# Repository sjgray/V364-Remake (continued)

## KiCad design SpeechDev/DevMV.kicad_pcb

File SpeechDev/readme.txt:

Commodore V364 Prototype Remake Project   Steve J. Gray
=======================================

This is a project to remake the V364 prototype computer from Commodore.
This would have been the flagship model in the TED/264 series, and
would feature a larger case with numeric keypad and built-in speech
synthesis using a more integrated version of the Magic Voice ("MV")
cartridge that was released for the C64.

SPEECH DEV BOARD
================

This is a development board that lets you experiment with adding speech to
any 264-series machine. It contains sockets for developing either type of
speech method:

* V364 - Uses V364 custom Gate Array and the Toshiba T6721A chips
* Magic Voice - Uses 6525 TPI, GI Logic Array and T6721A chips.

**** IMPORTANT!!! Install only the chips in the correct set!

CONNECTIONS
===========

The board is connected to one ROM socket of the 264 machine via a ribbon cable,
or using a header under the board (depending on computer and clearance).
The ROM from the computer is installed on the Dev board and the V364 Speech ROM
or modified speech ROM are installed in the other socket.

There are a bunch of flyouts to connect to various places on the computer pcb.

PLA F0 - The PLA F0 pin controls the 6525 or Custom Gate Array
CS_SPEECH - Connects to ROM control C2_HI.
R/W - Connect to Read/Write line.
PHI0 - Connect to PHI0 line.
IRQ - Connect to IRQ line.
AUDIO_IN - Normally not used but can connect to a SID board etc
AUDIO_OUT - Connects to EXT_AUDIO line (cartridge connector)

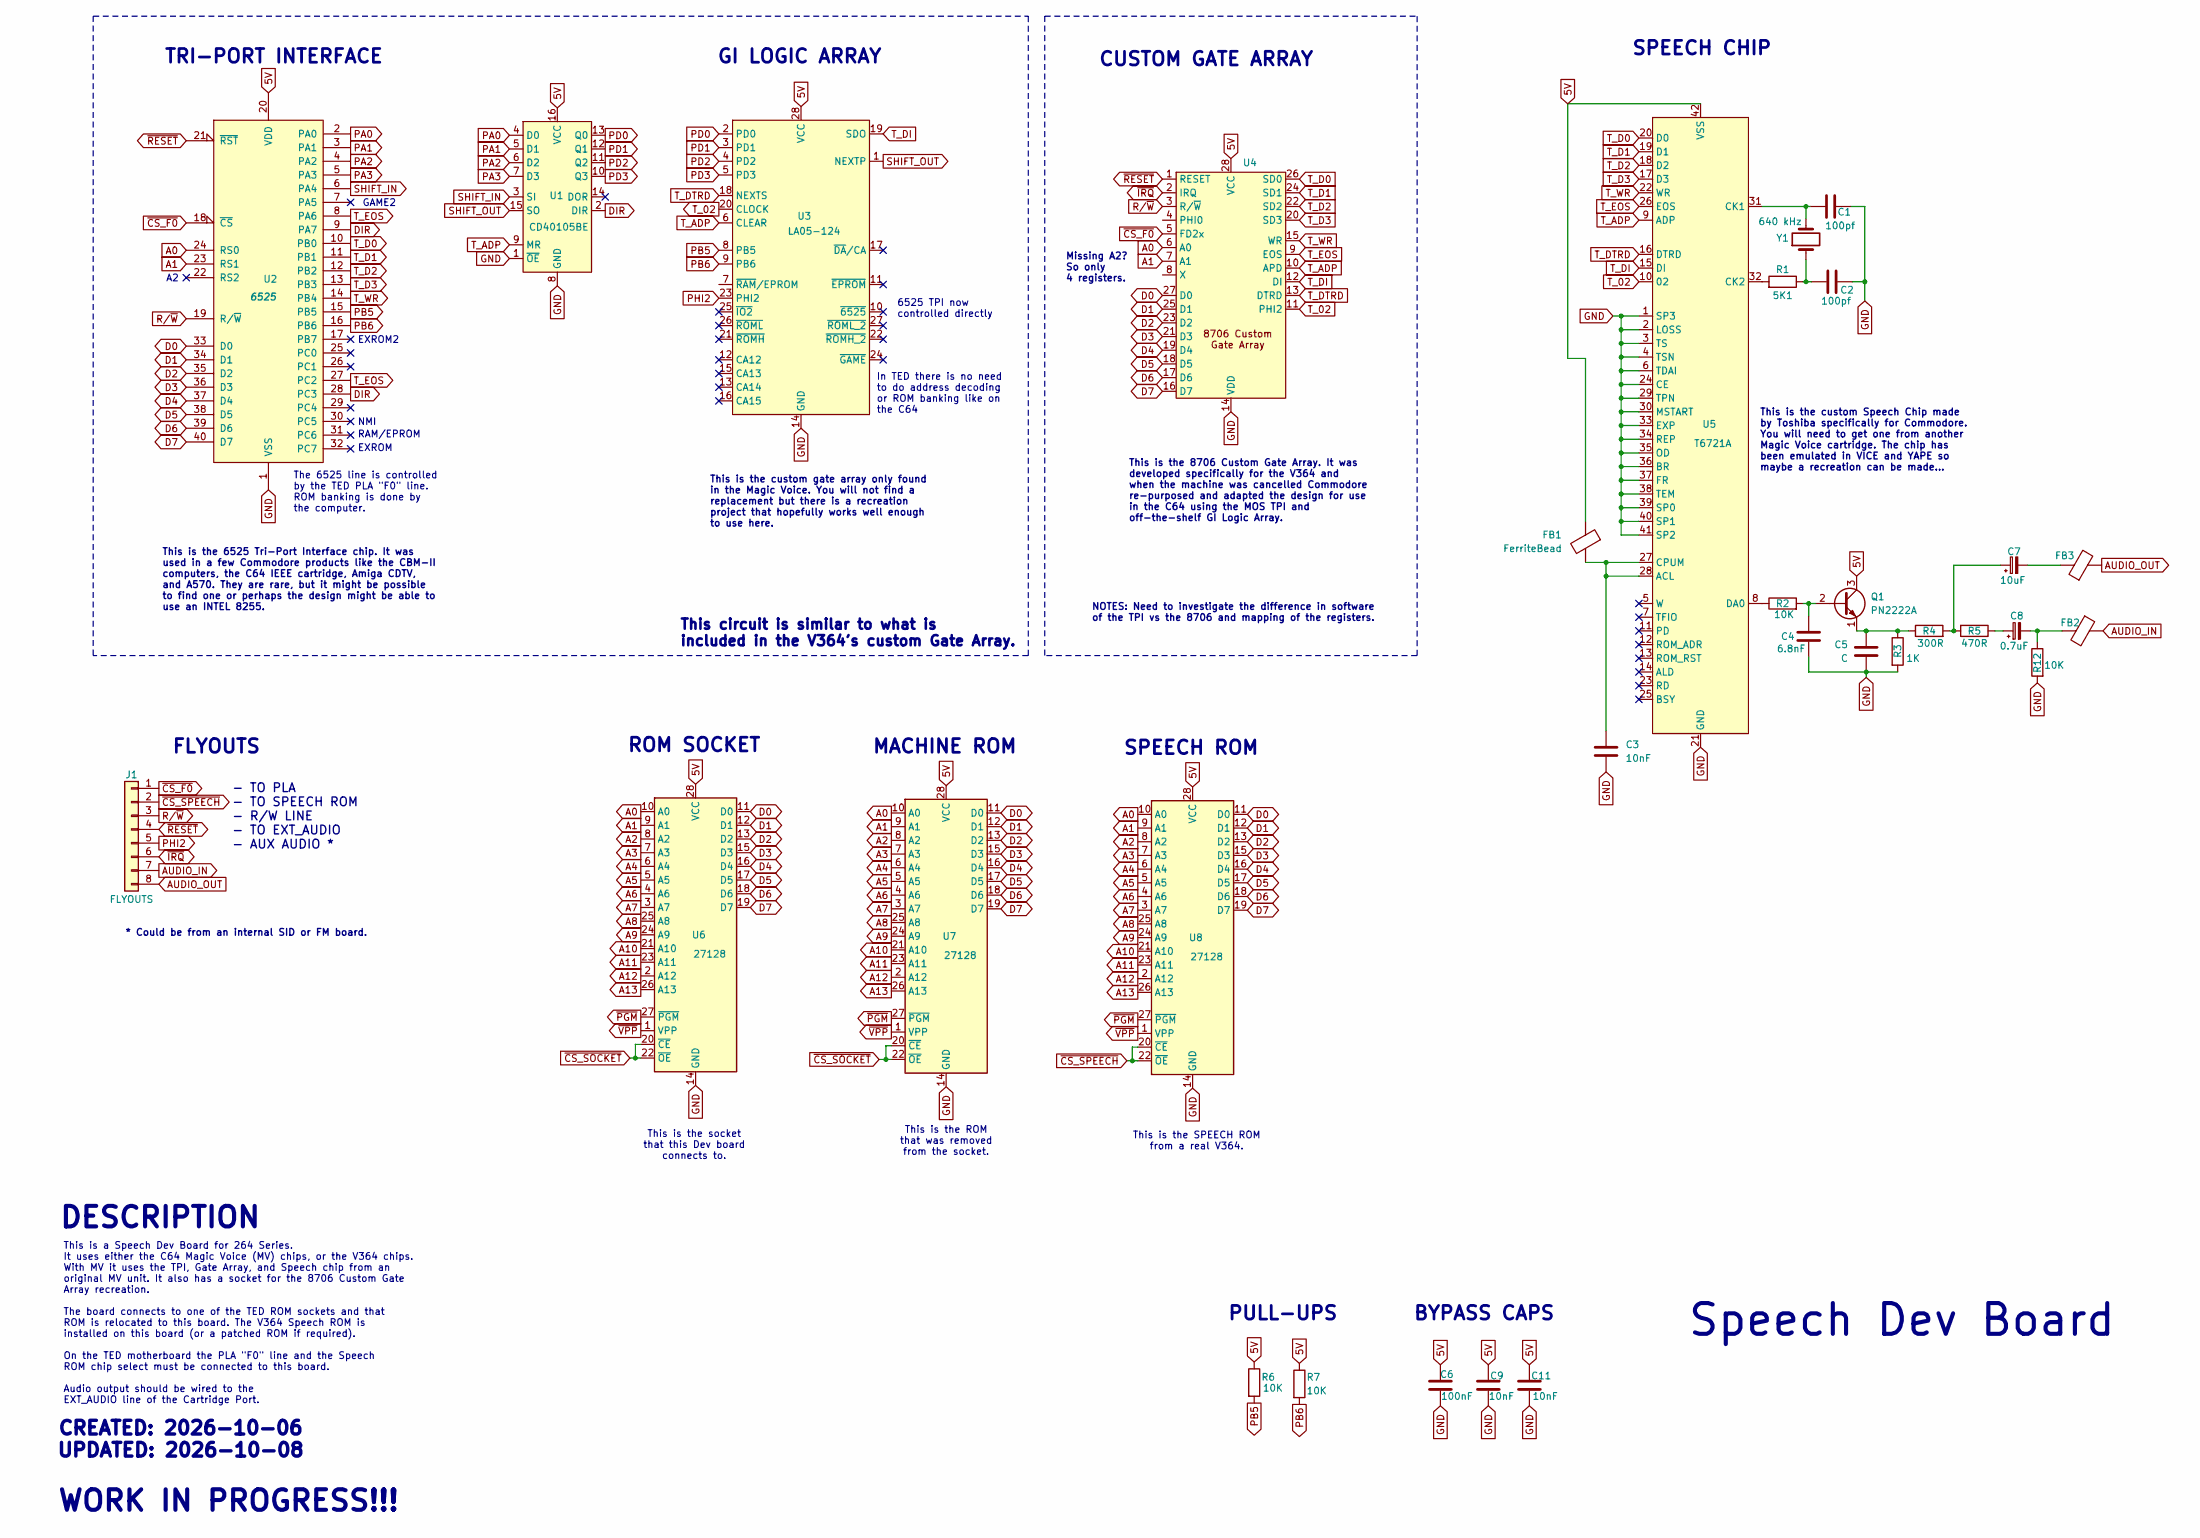
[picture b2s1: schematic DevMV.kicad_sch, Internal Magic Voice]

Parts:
C1, C2: 100pf; C_Disc_D5.0mm_W2.5mm_P5.00mm
C3, C11: 10nF; C_Disc_D5.1mm_W3.2mm_P5.00mm
C4: 6.8nF; C_Disc_D5.0mm_W2.5mm_P5.00mm
C5: C; C_Disc_D5.1mm_W3.2mm_P5.00mm
C6: 100nF; C_Disc_D5.1mm_W3.2mm_P5.00mm
C7: 10uF; CP_Radial_D8.0mm_P5.00mm
C8: 0.7uF; CP_Radial_D8.0mm_P5.00mm
C9: 10nF; C_Disc_D5.0mm_W2.5mm_P5.00mm
FB1, FB2, FB3: FerriteBead; R_Axial_DIN0309_L9.0mm_D3.2mm_P12.70mm_Horizontal
J1: FLYOUTS; PinHeader_1x08_P2.54mm_Vertical
Q1: PN2222A; TO-92_Inline_Wide
R1: 5K1; R_Axial_DIN0309_L9.0mm_D3.2mm_P12.70mm_Horizontal
R2, R6, R7, R12: 10K; R_Axial_DIN0309_L9.0mm_D3.2mm_P12.70mm_Horizontal
R3: 1K; R_Axial_DIN0309_L9.0mm_D3.2mm_P12.70mm_Horizontal
R4: 300R; R_Axial_DIN0309_L9.0mm_D3.2mm_P12.70mm_Horizontal
R5: 470R; R_Axial_DIN0309_L9.0mm_D3.2mm_P12.70mm_Horizontal
U1: CD40105BE; DIP-16_W7.62mm
U2: 6525; DIP-40_W15.24mm
U3: LA05-124; DIP-28_W15.24mm
U4: DIP-28_W15.24mm_LongPads
U5: T6721A; DIP-42_W15.24mm
U6, U7, U8: 27128; DIP-28_W15.24mm
Y1: 640 kHz; Crystal_HC18-U_Vertical

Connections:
5V: C6.1, C9.1, C11.1, FB1.1, Q1.3 (C), R6.1, R7.1, U1.16 (VCC), U2.20 (VDD), U3.28 (VCC), U4.28 (VCC), U5.42 (VSS), U6.28 (VCC), U7.28 (VCC), U8.28 (VCC)
A0: U2.24 (RS0), U4.6 (A0), U6.10 (A0), U7.10 (A0), U8.10 (A0)
A1: U2.23 (RS1), U4.7 (A1), U6.9 (A1), U7.9 (A1), U8.9 (A1)
A2: U6.8 (A2), U7.8 (A2), U8.8 (A2)
A3: U6.7 (A3), U7.7 (A3), U8.7 (A3)
A4: U6.6 (A4), U7.6 (A4), U8.6 (A4)
A5: U6.5 (A5), U7.5 (A5), U8.5 (A5)
A6: U6.4 (A6), U7.4 (A6), U8.4 (A6)
A7: U6.3 (A7), U7.3 (A7), U8.3 (A7)
A8: U6.25 (A8), U7.25 (A8), U8.25 (A8)
A9: U6.24 (A9), U7.24 (A9), U8.24 (A9)
A10: U6.21 (A10), U7.21 (A10), U8.21 (A10)
A11: U6.23 (A11), U7.23 (A11), U8.23 (A11)
A12: U6.2 (A12), U7.2 (A12), U8.2 (A12)
A13: U6.26 (A13), U7.26 (A13), U8.26 (A13)
AUDIO_IN: FB2.1, J1.7
AUDIO_OUT: FB3.2, J1.8
D0: U2.33 (D0), U4.27 (D0), U6.11 (D0), U7.11 (D0), U8.11 (D0)
D1: U2.34 (D1), U4.25 (D1), U6.12 (D1), U7.12 (D1), U8.12 (D1)
D2: U2.35 (D2), U4.23 (D2), U6.13 (D2), U7.13 (D2), U8.13 (D2)
D3: U2.36 (D3), U4.21 (D3), U6.15 (D3), U7.15 (D3), U8.15 (D3)
D4: U2.37 (D4), U4.19 (D4), U6.16 (D4), U7.16 (D4), U8.16 (D4)
D5: U2.38 (D5), U4.18 (D5), U6.17 (D5), U7.17 (D5), U8.17 (D5)
D6: U2.39 (D6), U4.17 (D6), U6.18 (D6), U7.18 (D6), U8.18 (D6)
D7: U2.40 (D7), U4.16 (D7), U6.19 (D7), U7.19 (D7), U8.19 (D7)
DIR: U1.2 (DIR), U2.9 (PA7), U2.28 (PC3)
GND: C1.1, C2.1, C3.2, C4.2, C5.2, C6.2, C9.2, C11.2, R3.2, R12.2, U1.1 (~OE), U1.8 (GND), U2.1 (VSS), U3.14 (GND), U4.14 (VDD), U5.1 (SP3), U5.2 (LOSS), U5.3 (TS), U5.4 (TSN), U5.6 (TDAI), U5.21 (GND), U5.24 (CE), U5.29 (TPN), U5.30 (MSTART), U5.33 (EXP), U5.34 (REP), U5.35 (OD), U5.36 (BR), U5.37 (FR), U5.38 (TEM), U5.39 (SP0), U5.40 (SP1), U5.41 (SP2), U6.14 (GND), U7.14 (GND), U8.14 (GND)
unnamed: C2.2, R1.1, Y1.1
unnamed: C7.1, R4.2, R5.2
unnamed: C7.2, FB3.1
unnamed: C8.1, R5.1
unnamed: C8.2, FB2.2, R12.1
unnamed: C4.1, Q1.2 (B), R2.2
unnamed: C5.1, Q1.1 (E), R3.1, R4.1
unnamed: C3.1, FB1.2, U5.27 (CPUM), U5.28 (ACL)
unnamed: C1.2, U5.31 (CK1), Y1.2
unnamed: R1.2, U5.32 (CK2)
unnamed: R2.1, U5.8 (DA0)
PA0: U1.4 (D0), U2.2 (PA0)
PA1: U1.5 (D1), U2.3 (PA1)
PA2: U1.6 (D2), U2.4 (PA2)
PA3: U1.7 (D3), U2.5 (PA3)
PB5: R6.2, U2.15 (PB5), U3.8 (PB5)
PB6: R7.2, U2.16 (PB6), U3.9 (PB6)
PD0: U1.13 (Q0), U3.2 (PD0)
PD1: U1.12 (Q1), U3.3 (PD1)
PD2: U1.11 (Q2), U3.4 (PD2)
PD3: U1.10 (Q3), U3.5 (PD3)
PHI2: J1.5, U3.23 (PHI2)
R/~W: J1.3, U2.19 (R/~W), U4.3 (R/~W)
SHIFT_IN: U1.3 (SI), U2.6 (PA4)
SHIFT_OUT: U1.15 (SO), U3.1 (NEXTP)
T_02: U3.20 (CLOCK), U4.11 (PHI2), U5.10 (02)
T_ADP: U1.9 (MR), U3.6 (CLEAR), U4.10 (APD), U5.9 (ADP)
T_D0: U2.10 (PB0), U4.26 (SD0), U5.20 (D0)
T_D1: U2.11 (PB1), U4.24 (SD1), U5.19 (D1)
T_D2: U2.12 (PB2), U4.22 (SD2), U5.18 (D2)
T_D3: U2.13 (PB3), U4.20 (SD3), U5.17 (D3)
T_DI: U3.19 (SDO), U4.12 (DI), U5.15 (DI)
T_DTRD: U3.18 (NEXTS), U4.13 (DTRD), U5.16 (DTRD)
T_EOS: U2.8 (PA6), U2.27 (PC2), U4.9 (EOS), U5.26 (EOS)
T_WR: U2.14 (PB4), U4.15 (WR), U5.22 (WR)
~CS_F0: J1.1, U2.18 (~CS), U4.5 (FD2x)
~CS_SOCKET: U6.20 (~CE), U6.22 (~OE), U7.20 (~CE), U7.22 (~OE)
~CS_SPEECH: J1.2, U8.20 (~CE), U8.22 (~OE)
~IRQ: J1.6, U4.2 (IRQ)
~PGM: U6.27 (~PGM), U7.27 (~PGM), U8.27 (~PGM)
~RESET: J1.4, U2.21 (~RST), U4.1 (RESET)
~VPP: U6.1 (VPP), U7.1 (VPP), U8.1 (VPP)

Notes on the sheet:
FLYOUTS
The 6525 line is controlled by the TED PLA "F0" line. ROM banking is done by the computer.
This is a Speech Dev Board for 264 Series. It uses either the C64 Magic Voice (MV) chips, or the V364 chips. With MV it uses the TPI, Gate Array, and Speech chip from an original MV unit. It also has a socket for the 8706 Custom Gate Array recreation. The board connects to one of the TED ROM socket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
This circuit is similar to what is included in the V364's custom Gate Array.
This is the SPEECH ROM from a real V364.
WORK IN PROGRESS!!!
Speech Dev Board
CUSTOM GATE ARRAY
TRI-PORT INTERFACE
GI LOGIC ARRAY
This is the custom gate array only found in the Magic Voice. You will not find a replacement but there is a recreation project that hopefully works well enough to use here.
This is the 8706 Custom Gate Array. It was developed specifically for the V364 and when the machine was cancelled Commodore re-purposed and adapted the design for use in the C64 using the MOS TPI and off-the-shelf GI Logic Array.
EXROM2
BYPASS CAPS
EXROM
ROM SOCKET
- TO PLA - TO SPEECH ROM - R/W LINE - TO EXT_AUDIO - AUX AUDIO *
MACHINE ROM
Missing A2? So only 4 registers.
RAM/EPROM
SPEECH ROM
This is the custom Speech Chip made by Toshiba specifically for Commodore. You will need to get one from another Magic Voice cartridge. The chip has been emulated in VICE and YAPE so maybe a recreation can be made...
* Could be from an internal SID or FM board.
PULL-UPS
NOTES: Need to investigate the difference in software of the TPI vs the 8706 and mapping of the registers.
SPEECH CHIP
6525 TPI now controlled directly
NMI
CREATED: 2026-10-06 UPDATED: 2026-10-08
This is the socket that this Dev board connects to.
DESCRIPTION
This is the ROM that was removed from the socket.
This is the 6525 Tri-Port Interface chip. It was used in a few Commodore products like the CBM-II computers, the C64 IEEE cartridge, Amiga CDTV, and A570. They are rare, but it might be possible to find one or perhaps the design might be able to use an INTEL 8255.
In TED there is no need to do address decoding or ROM banking like on the C64
GAME2

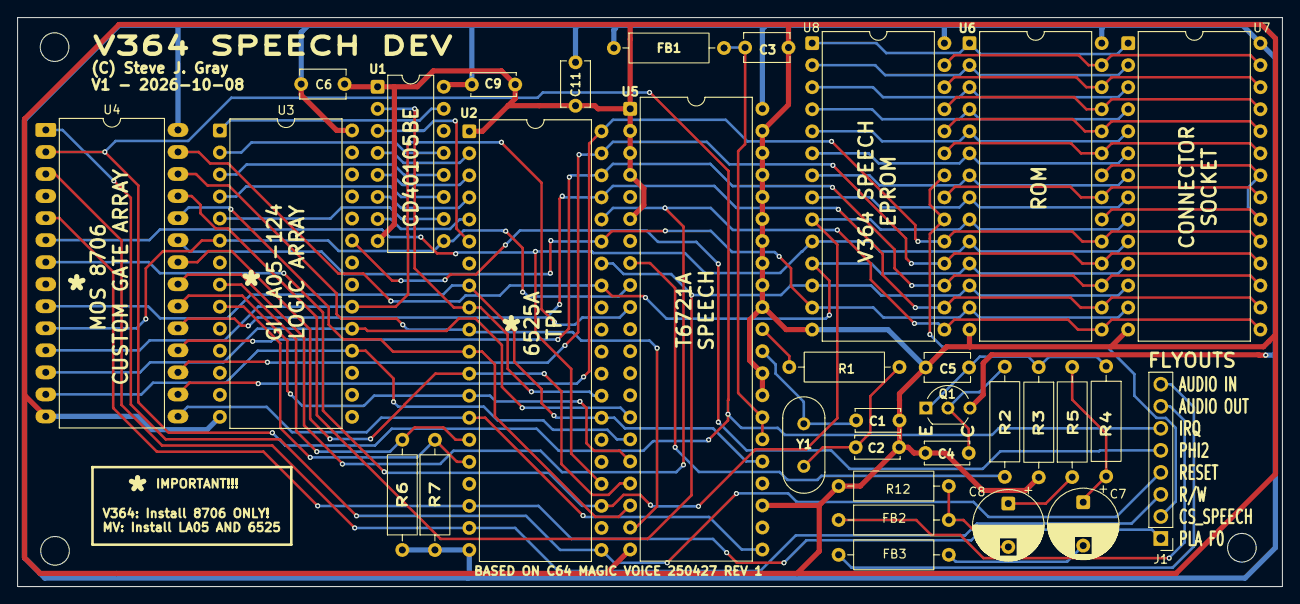
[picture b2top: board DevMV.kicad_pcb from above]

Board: 2 copper layers, 145.8 x 65.6 mm, 32 parts (0 on the bottom side), 69 nets.

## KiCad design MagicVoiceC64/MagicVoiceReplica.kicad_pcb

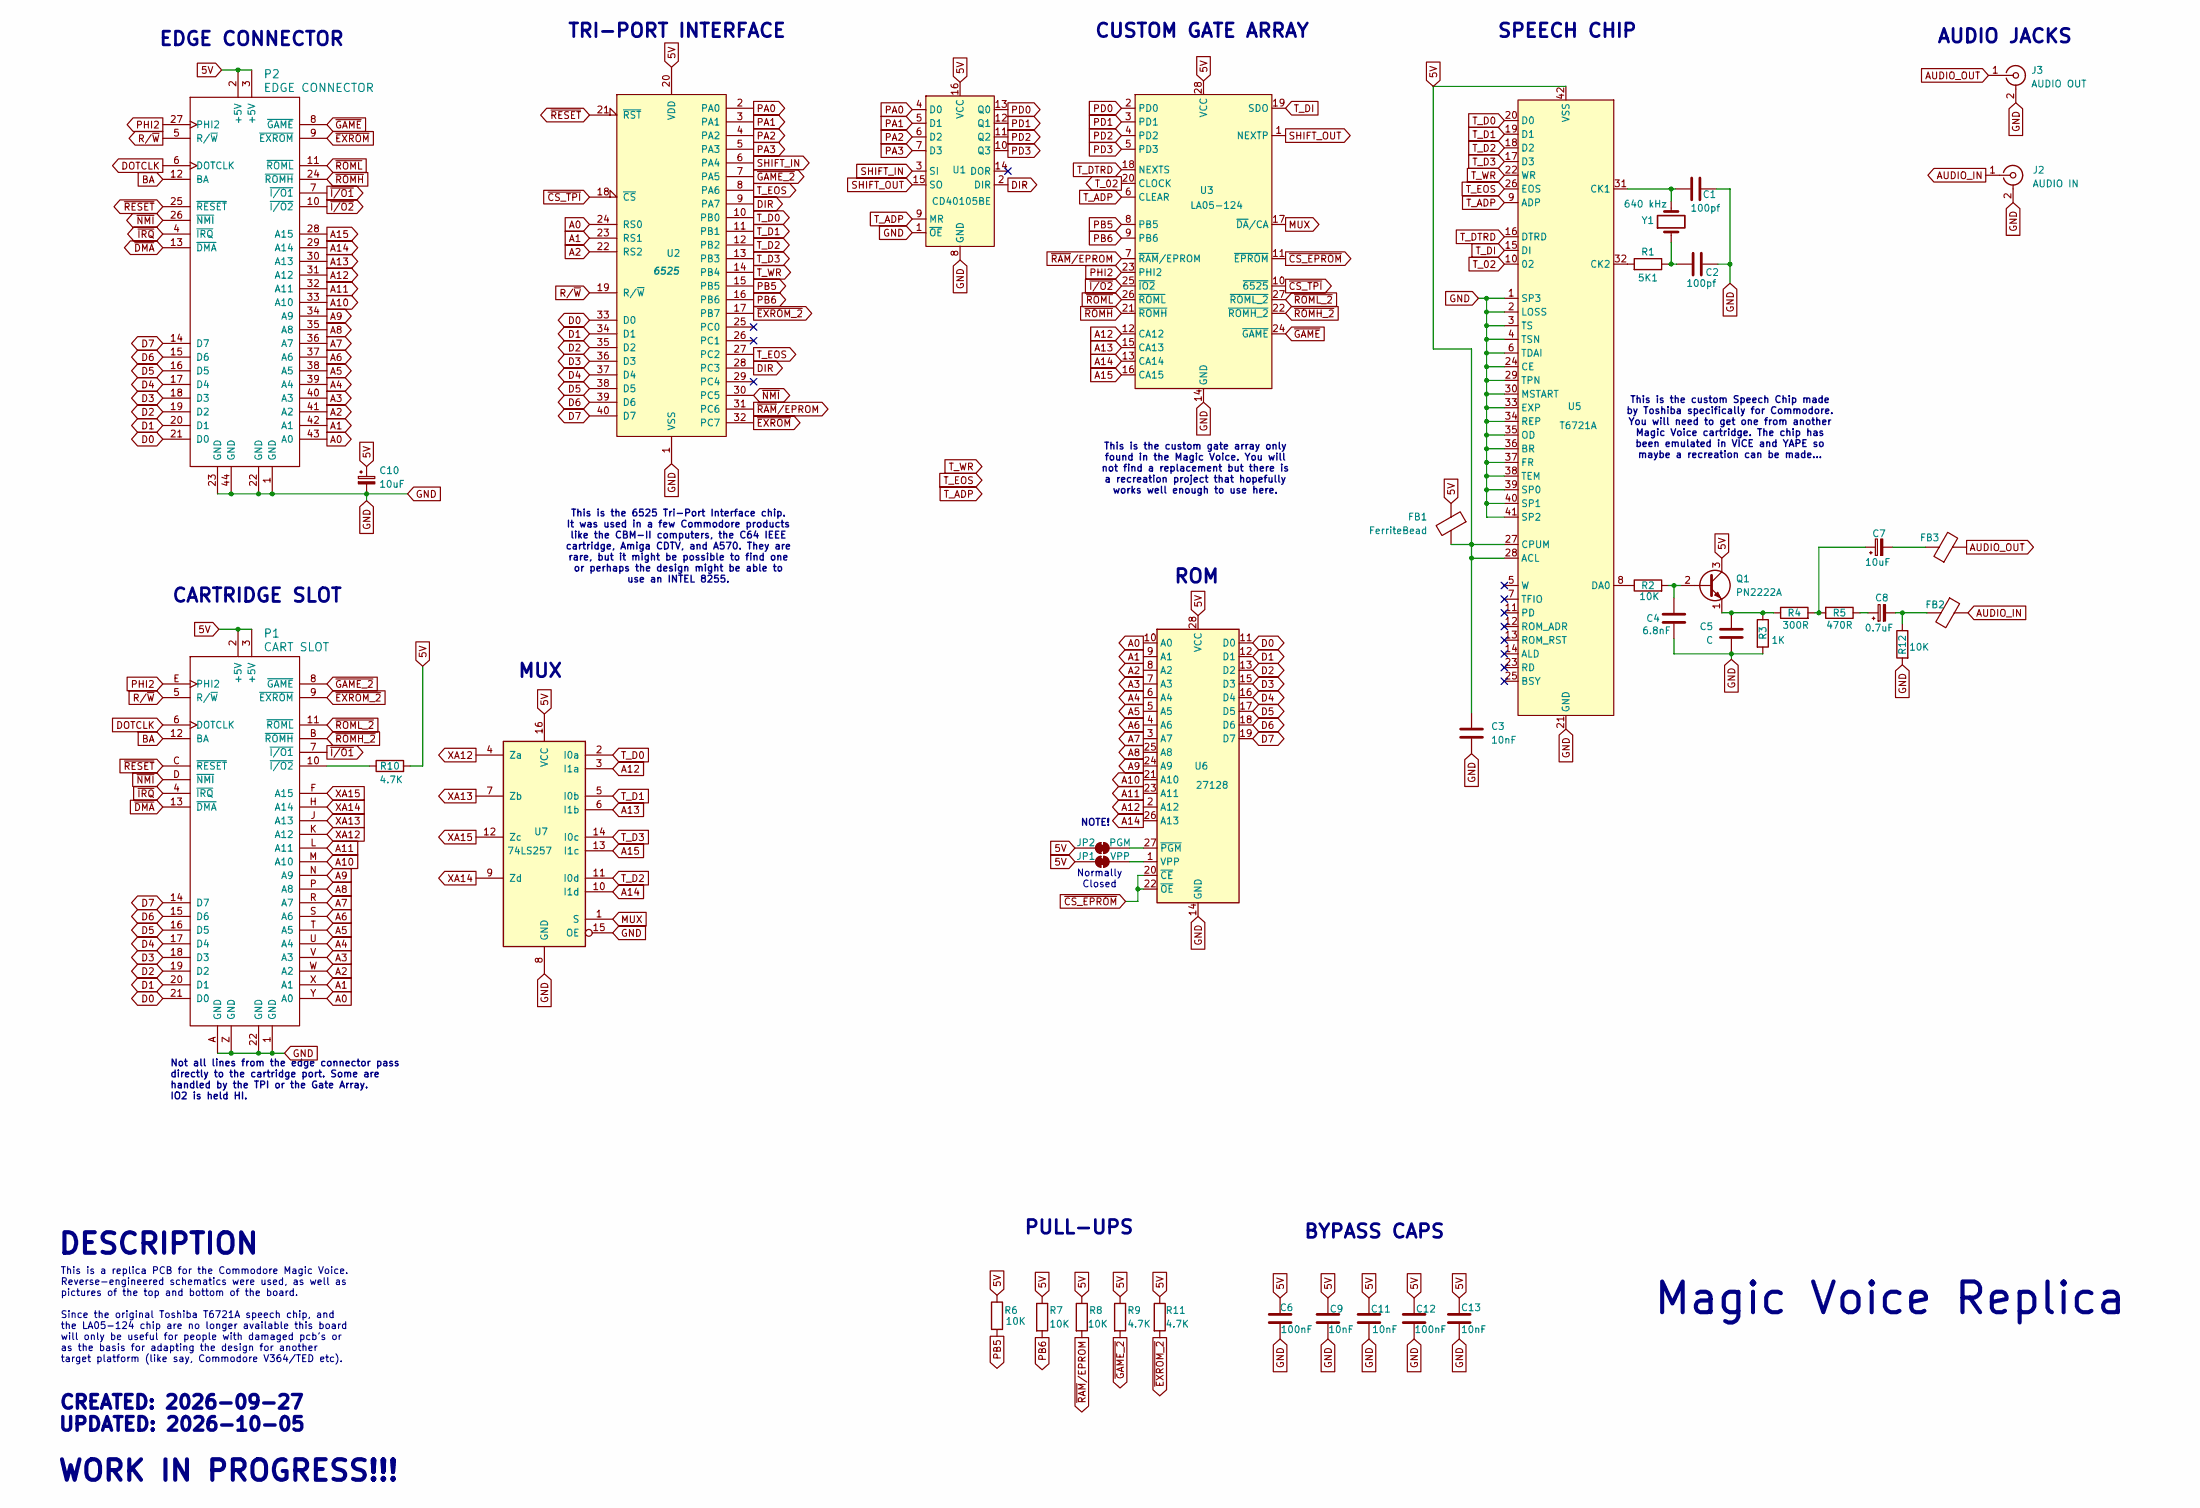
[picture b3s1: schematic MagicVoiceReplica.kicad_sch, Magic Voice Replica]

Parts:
C1, C2: 100pf; C_Disc_D5.0mm_W2.5mm_P5.00mm
C3, C11: 10nF; C_Disc_D5.1mm_W3.2mm_P5.00mm
C4: 6.8nF; C_Disc_D5.0mm_W2.5mm_P5.00mm
C5: C; C_Disc_D5.1mm_W3.2mm_P5.00mm
C6, C12: 100nF; C_Disc_D5.1mm_W3.2mm_P5.00mm
C7: 10uF; CP_Radial_D8.0mm_P5.00mm
C8: 0.7uF; CP_Radial_D8.0mm_P5.00mm
C9, C13: 10nF; C_Disc_D5.0mm_W2.5mm_P5.00mm
C10: 10uF; CP_Radial_D5.0mm_P2.00mm
FB1, FB2, FB3: FerriteBead; R_Axial_DIN0309_L9.0mm_D3.2mm_P12.70mm_Horizontal
J2: AUDIO IN; rca_white
J3: AUDIO OUT; rca_red
JP1: VPP; SolderJumper-2_P1.3mm_Bridged_RoundedPad1.0x1.5mm
JP2: PGM; SolderJumper-2_P1.3mm_Bridged_RoundedPad1.0x1.5mm
P1: CART SLOT; EXPANSION_PORT
P2: EDGE CONNECTOR; c64cartedge
Q1: PN2222A; TO-92_Inline_Wide
R1: 5K1; R_Axial_DIN0309_L9.0mm_D3.2mm_P12.70mm_Horizontal
R2, R6, R7, R8, R12: 10K; R_Axial_DIN0309_L9.0mm_D3.2mm_P12.70mm_Horizontal
R3: 1K; R_Axial_DIN0309_L9.0mm_D3.2mm_P12.70mm_Horizontal
R4: 300R; R_Axial_DIN0309_L9.0mm_D3.2mm_P12.70mm_Horizontal
R5: 470R; R_Axial_DIN0309_L9.0mm_D3.2mm_P12.70mm_Horizontal
R9, R10, R11: 4.7K; R_Axial_DIN0309_L9.0mm_D3.2mm_P12.70mm_Horizontal
U1: CD40105BE; DIP-16_W7.62mm
U2: 6525; DIP-40_W15.24mm
U3: LA05-124; DIP-28_W15.24mm
U5: T6721A; DIP-42_W15.24mm
U6: 27128; DIP-28_W15.24mm
U7: 74LS257; DIP-16_W7.62mm
Y1: 640 kHz; Crystal_HC18-U_Vertical

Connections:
5V: C3.1, C6.1, C9.1, C10.1, C11.1, C12.1, C13.1, FB1.1, FB1.2, JP1.1 (A), JP2.1 (A), P1.2 (+5V), P1.3 (+5V), P2.2 (+5V), P2.3 (+5V), Q1.3 (C), R6.1, R7.1, R8.1, R9.1, R10.2, R11.1, U1.16 (VCC), U2.20 (VDD), U3.28 (VCC), U5.27 (CPUM), U5.28 (ACL), U5.42 (VSS), U6.28 (VCC), U7.16 (VCC)
A0: P1.Y (A0), P2.43 (A0), U2.24 (RS0), U6.10 (A0)
A1: P1.X (A1), P2.42 (A1), U2.23 (RS1), U6.9 (A1)
A2: P1.W (A2), P2.41 (A2), U2.22 (RS2), U6.8 (A2)
A3: P1.V (A3), P2.40 (A3), U6.7 (A3)
A4: P1.U (A4), P2.39 (A4), U6.6 (A4)
A5: P1.T (A5), P2.38 (A5), U6.5 (A5)
A6: P1.S (A6), P2.37 (A6), U6.4 (A6)
A7: P1.R (A7), P2.36 (A7), U6.3 (A7)
A8: P1.P (A8), P2.35 (A8), U6.25 (A8)
A9: P1.N (A9), P2.34 (A9), U6.24 (A9)
A10: P1.M (A10), P2.33 (A10), U6.21 (A10)
A11: P1.L (A11), P2.32 (A11), U6.23 (A11)
A12: P2.31 (A12), U3.12 (CA12), U6.2 (A12), U7.3 (I1a)
A13: P2.30 (A13), U3.15 (CA13), U7.6 (I1b)
A14: P2.29 (A14), U3.13 (CA14), U6.26 (A13), U7.10 (I1d)
A15: P2.28 (A15), U3.16 (CA15), U7.13 (I1c)
AUDIO_IN: FB2.1, J2.1 (In)
AUDIO_OUT: FB3.2, J3.1 (In)
BA: P1.12 (BA), P2.12 (BA)
D0: P1.21 (D0), P2.21 (D0), U2.33 (D0), U6.11 (D0)
D1: P1.20 (D1), P2.20 (D1), U2.34 (D1), U6.12 (D1)
D2: P1.19 (D2), P2.19 (D2), U2.35 (D2), U6.13 (D2)
D3: P1.18 (D3), P2.18 (D3), U2.36 (D3), U6.15 (D3)
D4: P1.17 (D4), P2.17 (D4), U2.37 (D4), U6.16 (D4)
D5: P1.16 (D5), P2.16 (D5), U2.38 (D5), U6.17 (D5)
D6: P1.15 (D6), P2.15 (D6), U2.39 (D6), U6.18 (D6)
D7: P1.14 (D7), P2.14 (D7), U2.40 (D7), U6.19 (D7)
DIR: U1.2 (DIR), U2.9 (PA7), U2.28 (PC3)
DOTCLK: P1.6 (DOTCLK), P2.6 (DOTCLK)
GND: C1.1, C2.1, C3.2, C4.2, C5.2, C6.2, C9.2, C10.2, C11.2, C12.2, C13.2, J2.2 (Ext), J3.2 (Ext), P1.1 (GND), P1.22 (GND), P1.A (GND), P1.Z (GND), P2.1 (GND), P2.22 (GND), P2.23 (GND), P2.44 (GND), R3.2, R12.2, U1.1 (~OE), U1.8 (GND), U2.1 (VSS), U3.14 (GND), U5.1 (SP3), U5.2 (LOSS), U5.3 (TS), U5.4 (TSN), U5.6 (TDAI), U5.21 (GND), U5.24 (CE), U5.29 (TPN), U5.30 (MSTART), U5.33 (EXP), U5.34 (REP), U5.35 (OD), U5.36 (BR), U5.37 (FR), U5.38 (TEM), U5.39 (SP0), U5.40 (SP1), U5.41 (SP2), U6.14 (GND), U7.8 (GND), U7.15 (OE)
MUX: U3.17 (~DA/CA), U7.1 (S)
unnamed: C2.2, R1.1, Y1.1
unnamed: C7.1, R4.2, R5.2
unnamed: C7.2, FB3.1
unnamed: C8.1, R5.1
unnamed: C8.2, FB2.2, R12.1
unnamed: JP1.2 (B), U6.1 (VPP)
unnamed: JP2.2 (B), U6.27 (~PGM)
unnamed: P1.10 (~I/O2), R10.1
unnamed: C4.1, Q1.2 (B), R2.2
unnamed: C5.1, Q1.1 (E), R3.1, R4.1
unnamed: C1.2, U5.31 (CK1), Y1.2
unnamed: R1.2, U5.32 (CK2)
unnamed: R2.1, U5.8 (DA0)
PA0: U1.4 (D0), U2.2 (PA0)
PA1: U1.5 (D1), U2.3 (PA1)
PA2: U1.6 (D2), U2.4 (PA2)
PA3: U1.7 (D3), U2.5 (PA3)
PB5: R6.2, U2.15 (PB5), U3.8 (PB5)
PB6: R7.2, U2.16 (PB6), U3.9 (PB6)
PD0: U1.13 (Q0), U3.2 (PD0)
PD1: U1.12 (Q1), U3.3 (PD1)
PD2: U1.11 (Q2), U3.4 (PD2)
PD3: U1.10 (Q3), U3.5 (PD3)
PHI2: P1.E (PHI2), P2.27 (PHI2), U3.23 (PHI2)
R/~W: P1.5 (R/~W), P2.5 (R/~W), U2.19 (R/~W)
SHIFT_IN: U1.3 (SI), U2.6 (PA4)
SHIFT_OUT: U1.15 (SO), U3.1 (NEXTP)
T_02: U3.20 (CLOCK), U5.10 (02)
T_ADP: U1.9 (MR), U3.6 (CLEAR), U5.9 (ADP)
T_D0: U2.10 (PB0), U5.20 (D0), U7.2 (I0a)
T_D1: U2.11 (PB1), U5.19 (D1), U7.5 (I0b)
T_D2: U2.12 (PB2), U5.18 (D2), U7.11 (I0d)
T_D3: U2.13 (PB3), U5.17 (D3), U7.14 (I0c)
T_DI: U3.19 (SDO), U5.15 (DI)
T_DTRD: U3.18 (NEXTS), U5.16 (DTRD)
T_EOS: U2.8 (PA6), U2.27 (PC2), U5.26 (EOS)
T_WR: U2.14 (PB4), U5.22 (WR)
XA12: P1.K (A12), U7.4 (Za)
XA13: P1.J (A13), U7.7 (Zb)
XA14: P1.H (A14), U7.9 (Zd)
XA15: P1.F (A15), U7.12 (Zc)
~CS_EPROM: U3.11 (~EPROM), U6.20 (~CE), U6.22 (~OE)
~CS_TPI: U2.18 (~CS), U3.10 (~6525)
~DMA: P1.13 (~DMA), P2.13 (~DMA)
~EXROM_2: P1.9 (~EXROM), R11.2, U2.17 (PB7)
~EXROM: P2.9 (~EXROM), U2.32 (PC7)
~GAME_2: P1.8 (~GAME), R9.2, U2.7 (PA5)
~GAME: P2.8 (~GAME), U3.24 (~GAME)
~IRQ: P1.4 (~IRQ), P2.4 (~IRQ)
~I/O1: P1.7 (~I/O1), P2.7 (~I/O1)
~I/O2: P2.10 (~I/O2), U3.25 (~IO2)
~NMI: P1.D (~NMI), P2.26 (~NMI), U2.30 (PC5)
~RAM/EPROM: R8.2, U2.31 (PC6), U3.7 (~RAM/EPROM)
~RESET: P1.C (~RESET), P2.25 (~RESET), U2.21 (~RST)
~ROMH_2: P1.B (~ROMH), U3.22 (~ROMH_2)
~ROMH: P2.24 (~ROMH), U3.21 (~ROMH)
~ROML_2: P1.11 (~ROML), U3.27 (~ROML_2)
~ROML: P2.11 (~ROML), U3.26 (~ROML)

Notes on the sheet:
This is a replica PCB for the Commodore Magic Voice. Reverse-engineered schematics were used, as well as pictures of the top and bottom of the board. Since the original Toshiba T6721A speech chip, and the LA05-124 chip are no longer available this board will only be useful for people with damaged p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
CARTRIDGE SLOT
WORK IN PROGRESS!!!
Magic Voice Replica
TRI-PORT INTERFACE
CUSTOM GATE ARRAY
MUX
This is the custom gate array only found in the Magic Voice. You will not find a replacement but there is a recreation project that hopefully works well enough to use here.
BYPASS CAPS
ROM
Not all lines from the edge connector pass directly to the cartridge port. Some are handled by the TPI or the Gate Array. IO2 is held HI.
EDGE CONNECTOR
This is the custom Speech Chip made by Toshiba specifically for Commodore. You will need to get one from another Magic Voice cartridge. The chip has been emulated in VICE and YAPE so maybe a recreation can be made...
Normally Closed
AUDIO JACKS
PULL-UPS
NOTE!
SPEECH CHIP
CREATED: 2026-09-27 UPDATED: 2026-10-05
DESCRIPTION
This is the 6525 Tri-Port Interface chip. It was used in a few Commodore products like the CBM-II computers, the C64 IEEE cartridge, Amiga CDTV, and A570. They are rare, but it might be possible to find one or perhaps the design might be able to use an INTEL 8255.

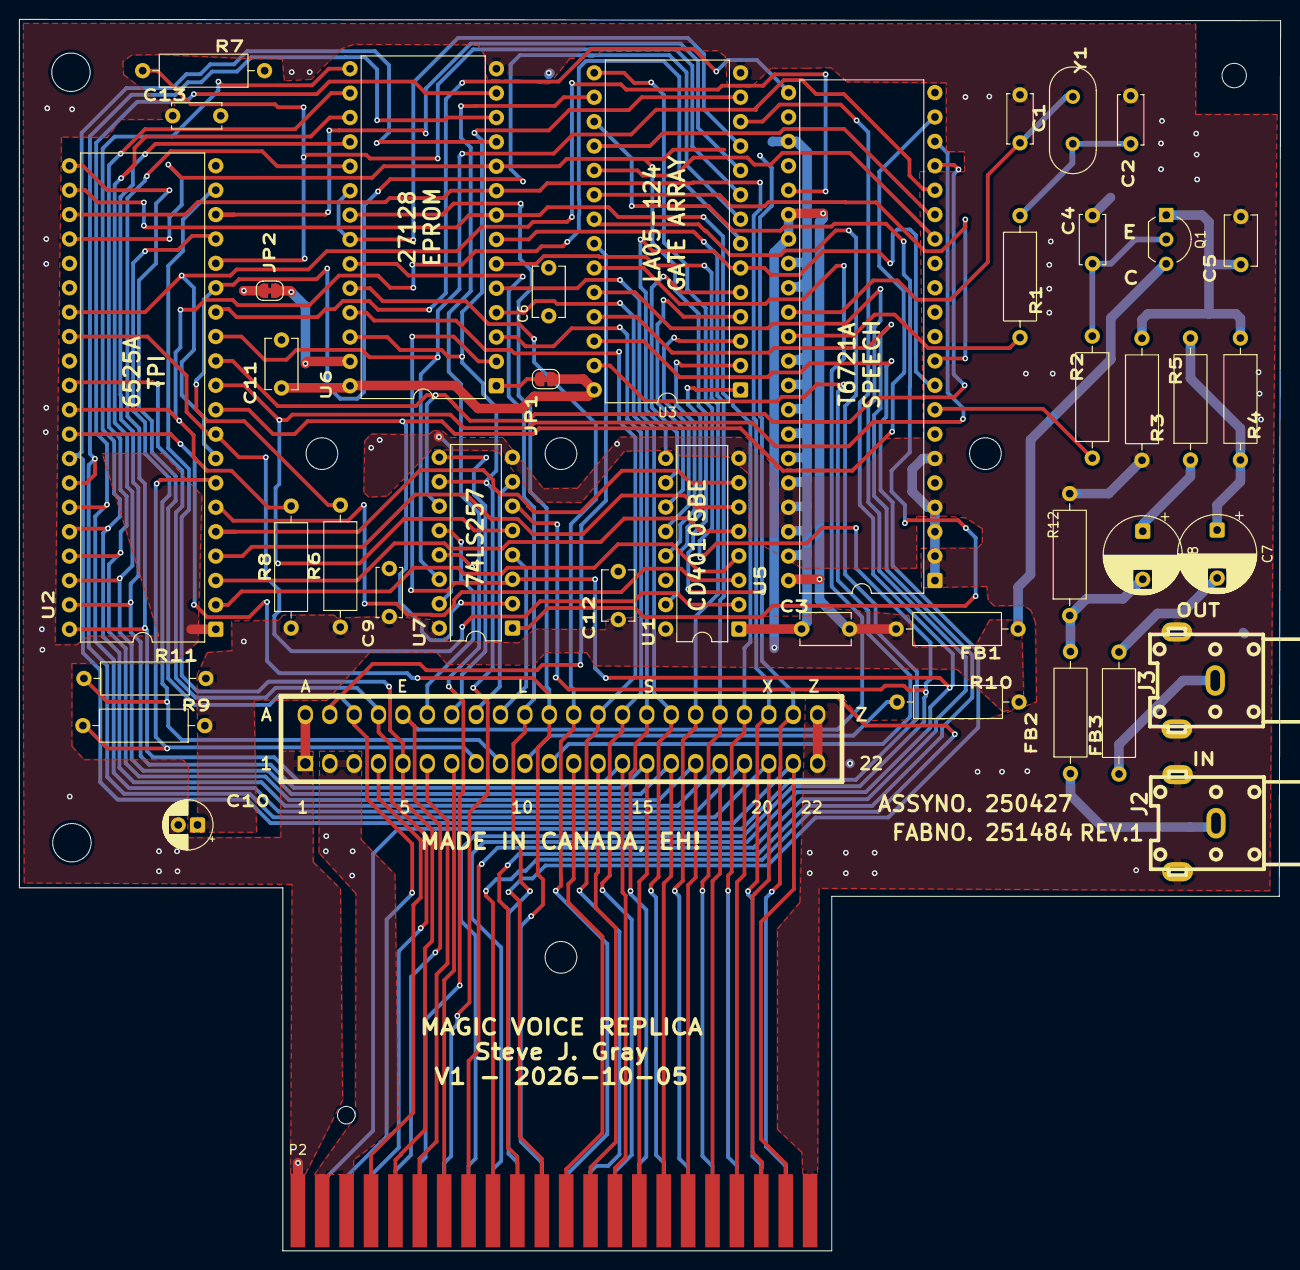
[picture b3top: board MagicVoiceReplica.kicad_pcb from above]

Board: 2 copper layers, 131.3 x 128.2 mm, 42 parts (0 on the bottom side), 90 nets.

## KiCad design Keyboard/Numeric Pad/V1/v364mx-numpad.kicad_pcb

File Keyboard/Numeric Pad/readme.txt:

Commodore V364 Prototype Remake Project   Steve J. Gray
=======================================

This is a project to remake the V364 prototype computer from Commodore.
This would have been the flagship model in the TED/264 series, and
would feature a larger case with numeric keypad and built-in speech
synthesis using a more integrated version of the Magic Voice cartridge
that was released for the C64.

Stand-alone Numeric Keypad
---------------------------

This has not been tested! Use at own risk.
The original "full" V364 keyboard was loaded and everything but the
numeric pad and one connecter were retained so there should be no
reason the numpad would not work, however it may require modifications
depending on the final case design.

The V364 motherboard should have an extra keyboard connector to connect
both a Plus/4 keyboard and this numeric pad. For Plus/4 motherboards it
will need a 2-to-1 adapter board to connect both.

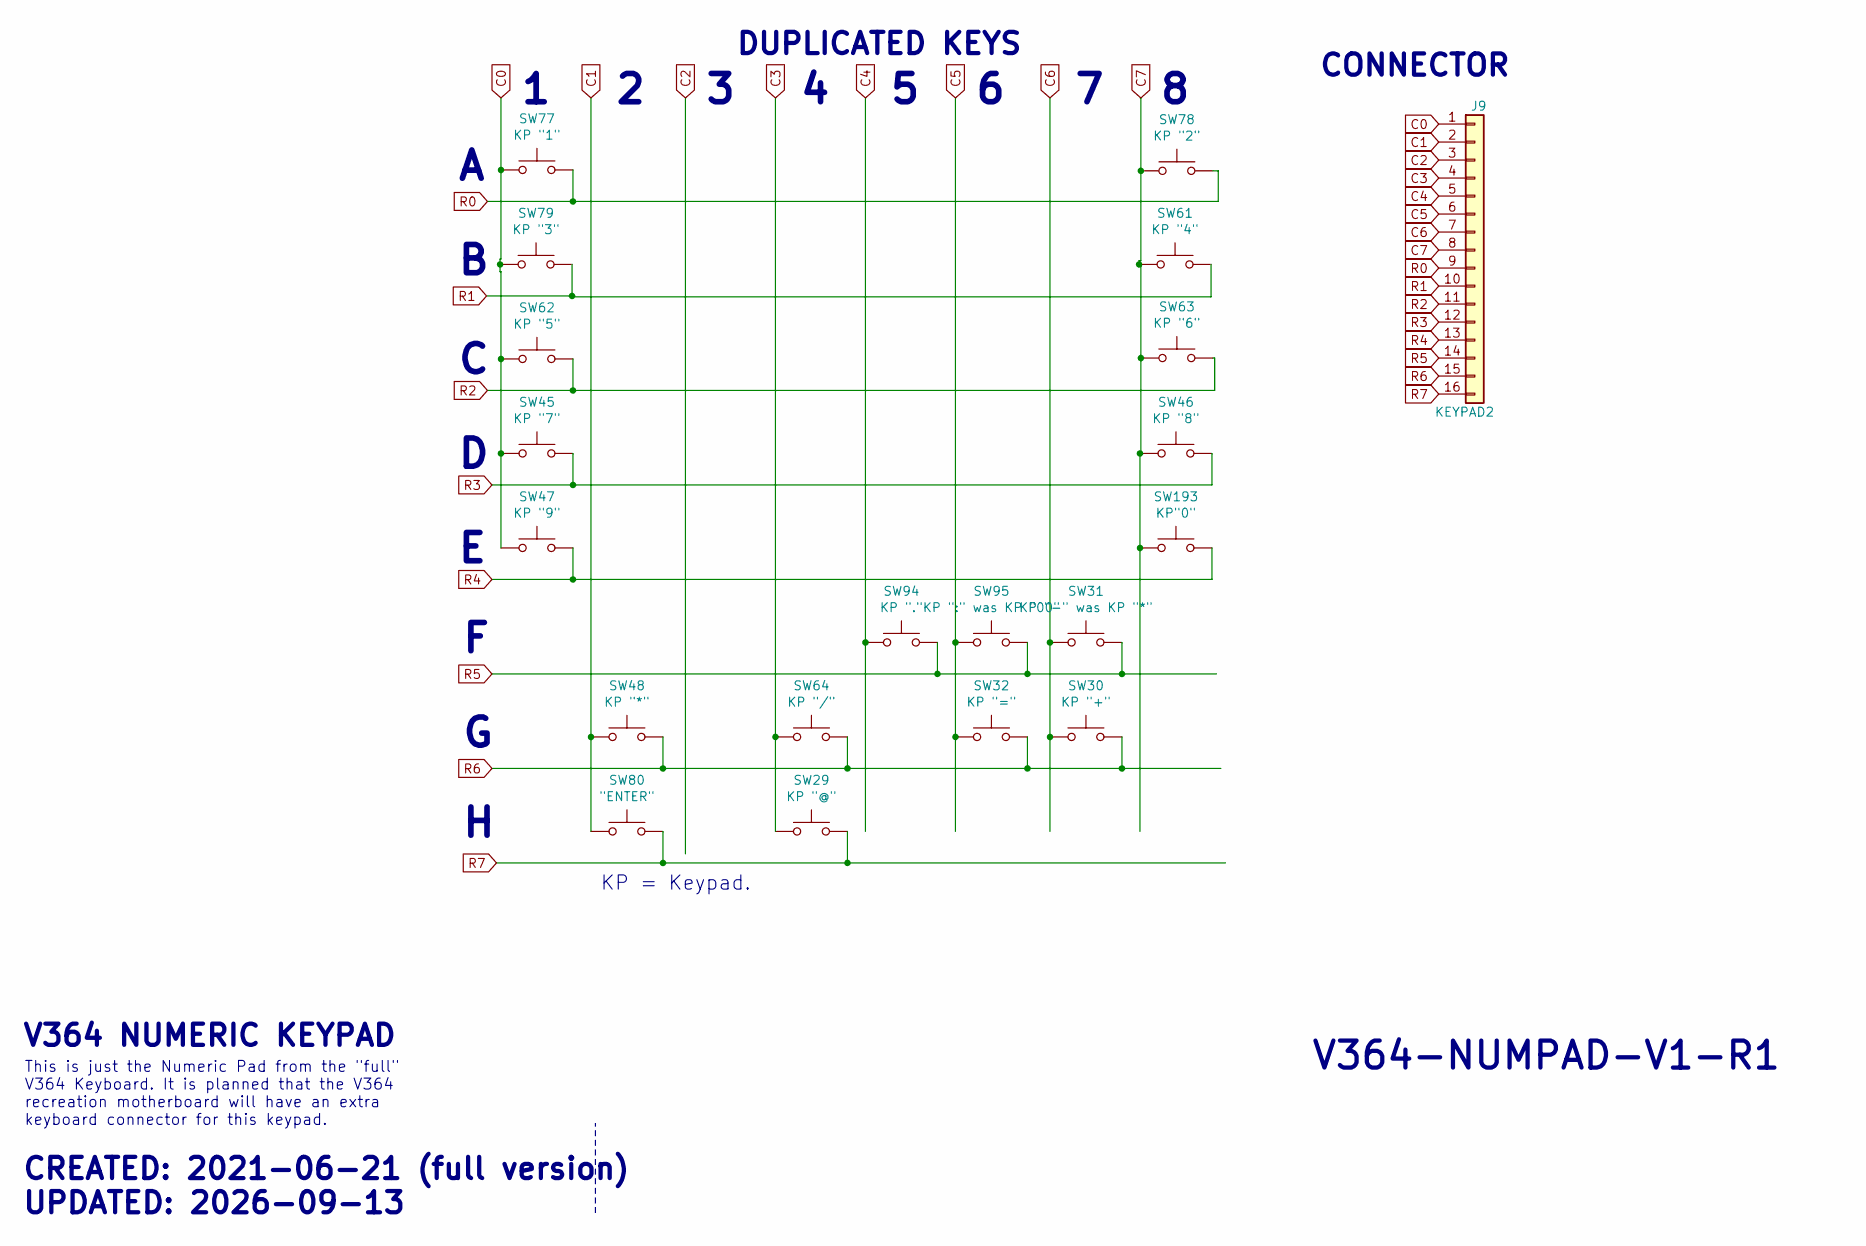
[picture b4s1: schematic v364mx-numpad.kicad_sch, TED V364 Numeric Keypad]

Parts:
J9: KEYPAD2; PinHeader_1x16_P2.54mm_Vertical
SW29: KP "@"; SW_Cherry_MX_1.00u_PCB
SW30: KP "+"; SW_Cherry_MX_1.00u_PCB
SW31: KP "-" was KP "*"; SW_Cherry_MX_1.00u_PCB
SW32: KP "="; SW_Cherry_MX_1.00u_PCB
SW45: KP "7"; SW_Cherry_MX_1.00u_PCB
SW46: KP "8"; SW_Cherry_MX_1.00u_PCB
SW47: KP "9"; SW_Cherry_MX_1.00u_PCB
SW48: KP "*"; SW_Cherry_MX_1.00u_PCB
SW61: KP "4"; SW_Cherry_MX_1.00u_PCB
SW62: KP "5"; SW_Cherry_MX_1.00u_PCB
SW63: KP "6"; SW_Cherry_MX_1.00u_PCB
SW64: KP "/"; SW_Cherry_MX_1.00u_PCB
SW77: KP "1"; SW_Cherry_MX_1.00u_PCB
SW78: KP "2"; SW_Cherry_MX_1.00u_PCB
SW79: KP "3"; SW_Cherry_MX_1.00u_PCB
SW80: "ENTER"; SW_Cherry_MX_2.00u_Vertical_PCB
SW94: KP "."; SW_Cherry_MX_1.00u_PCB
SW95: KP ":" was KP "00"; SW_Cherry_MX_1.00u_PCB
SW193: KP"0"; SW_Cherry_MX_1.00u_PCB

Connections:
C0: J9.1, SW45.1, SW47.1, SW62.1, SW77.1, SW79.1
C1: J9.2, SW48.1, SW80.1
C2: J9.3
C3: J9.4, SW29.1, SW64.1
C4: J9.5, SW94.1
C5: J9.6, SW32.1, SW95.1
C6: J9.7, SW30.1, SW31.1
C7: J9.8, SW46.1, SW61.1, SW63.1, SW78.1, SW193.1
R0: J9.9, SW77.2, SW78.2
R1: J9.10, SW61.2, SW79.2
R2: J9.11, SW62.2, SW63.2
R3: J9.12, SW45.2, SW46.2
R4: J9.13, SW47.2, SW193.2
R5: J9.14, SW31.2, SW94.2, SW95.2
R6: J9.15, SW30.2, SW32.2, SW48.2, SW64.2
R7: J9.16, SW29.2, SW80.2

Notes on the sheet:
KP = Keypad.
CONNECTOR
V364-NUMPAD-V1-R1
This is just the Numeric Pad from the "full" V364 Keyboard. It is planned that the V364 recreation motherboard will have an extra keyboard connector for this keypad.
DUPLICATED KEYS
V364 NUMERIC KEYPAD
CREATED: 2021-06-21 (full version) UPDATED: 2026-09-13

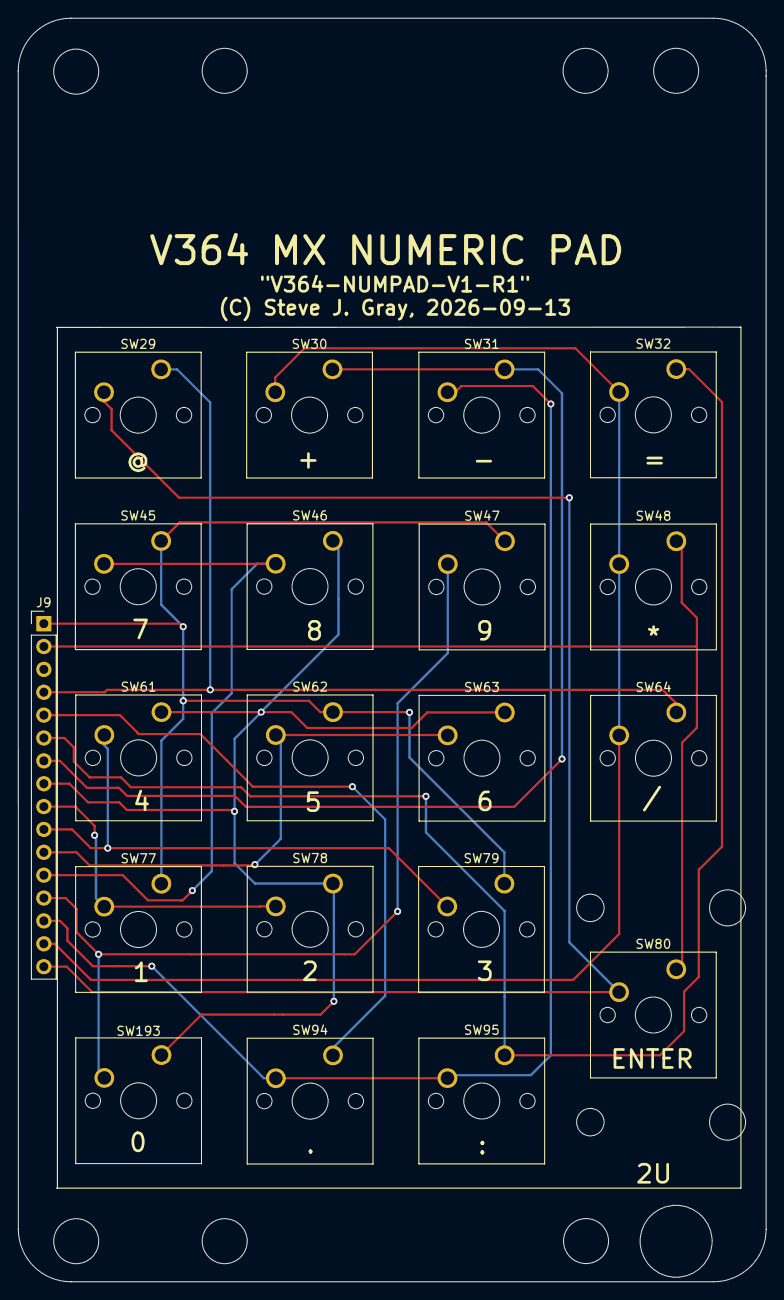
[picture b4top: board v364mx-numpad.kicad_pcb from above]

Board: 2 copper layers, 83.1 x 140.3 mm, 20 parts (0 on the bottom side), 15 nets.
